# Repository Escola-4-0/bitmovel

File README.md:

# BitMóvel
Com esta placa você pode fazer um robô controlado pela micro:bit que é fácil de montar e programar com a extensão Escola 4.0 para o MakeCode. A própria placa serve como chassi do robô e dispensa o uso de conectores especiais para a micro:bit. A pasta [bitmovel](https://github.com/Escola-4-0/bitmovel/tree/main/bitmovel) contém o projeto da PCB para o KiCAD e arquivos gerber prontos para fabricação.

As peças `para-choque.stl` e `suporte-sensor.stl` podem ser impressas em 3D para caracterizar seu robô e fixar sensores para fazê-lo funcionar como um seguidor de linha. 

## Características da placa (v3)
- Placa em face simples;
- Componentes em PTH para facilicar a montagem manual;
- Fixação da micro:bit usando parafusos;
- Fornece alimentação regulada 3.3V para a micro:bit;
- CI ponte-h para dois motores DC;
- Permite a conexão de sensores para seguidor de linha.

## Lista de materiais

REF | componente
-- | --
C1 | Capacitor eletrolítico 10uF - 10V |
C2 | Capacitor eletrolítico 10uF - 10V |
C3 | Capacitor eletrolítico 10uF - 10V |
D1 | LED difuso 5mm
D2 | LED difuso 5mm
D3 | Diodo 1N5817 (1N5818 - 1N5822 compatíveis)
J1 | Módulo adaptador micro-USB fêmea para DIP (opcional)
R1 | Resistor 330Ω
R2 | Resistor 330Ω
SW1 | Chave HH SS12F46 - 3 terminais
U1 | LM1117-3.3 (regulador de tensão 3.3V)
U2 | L293D (driver para motor DC)

Para implementar a função de seguidor de linha, são necessários ainda **2 módulos de sensor infravermelho TCRT5000**.

## Descrição e funcionamento
Seis pinos da micro:bit fornecem os sinais de entrada do driver L293D que controla os motores, conforme a tabela: 

pino micro:bit | pino L293D
:--: | :--:
P0 | 2A
P1 | 1A
P2 | 4A
P8 | 1,2EN
P13 | 3A
P15 | 3,4EN

A micro:bit é alimentada pelo regulador LM1117 de 3.3V, o driver L293D e os LEDs são alimentados diretamente pela tensão de entrada, a fonte deve ser de 4.5 a 7V.

Os pinos P14 e P16 recebem os sinais digitais do sensor infravermelho direito e esquerdo, respectivamente.

## Programação
A tabela abaixo resume os comandos para acionamento dos motores:

P8 (P15) | P0 (P2) | P1 (P13) | motor D (motor E)
:--: | :--: | :--: | --
PWM | 1 | 0 | girar horário*
PWM | 0 | 1 | girar anti-horário*
1 | 1 | 1 | parada forçada
1 | 0 | 0 | parada forçada
0 | X | X | parada livre

*O sentido real depende da ligação do motor. X = não importa.

Os sinais dos sensores infravermelho seguem a lógica da tabela abaixo:

P14 (P16) | sensor D (sensor E)
:--: | :--:
0 | luz refletindo, superfície clara
1 | luz não refletindo, superfície escura

No MakeCode, o BitMóvel pode ser programado com os blocos `gravação digital pin` e `gravação analógica pin`, seguindo as combinações da tabela acima, ou com a [extensão Escola 4.0](https://github.com/Escola-4-0/pxt-Escola_4pontozero), usando os blocos da categoria "BitMóvel".

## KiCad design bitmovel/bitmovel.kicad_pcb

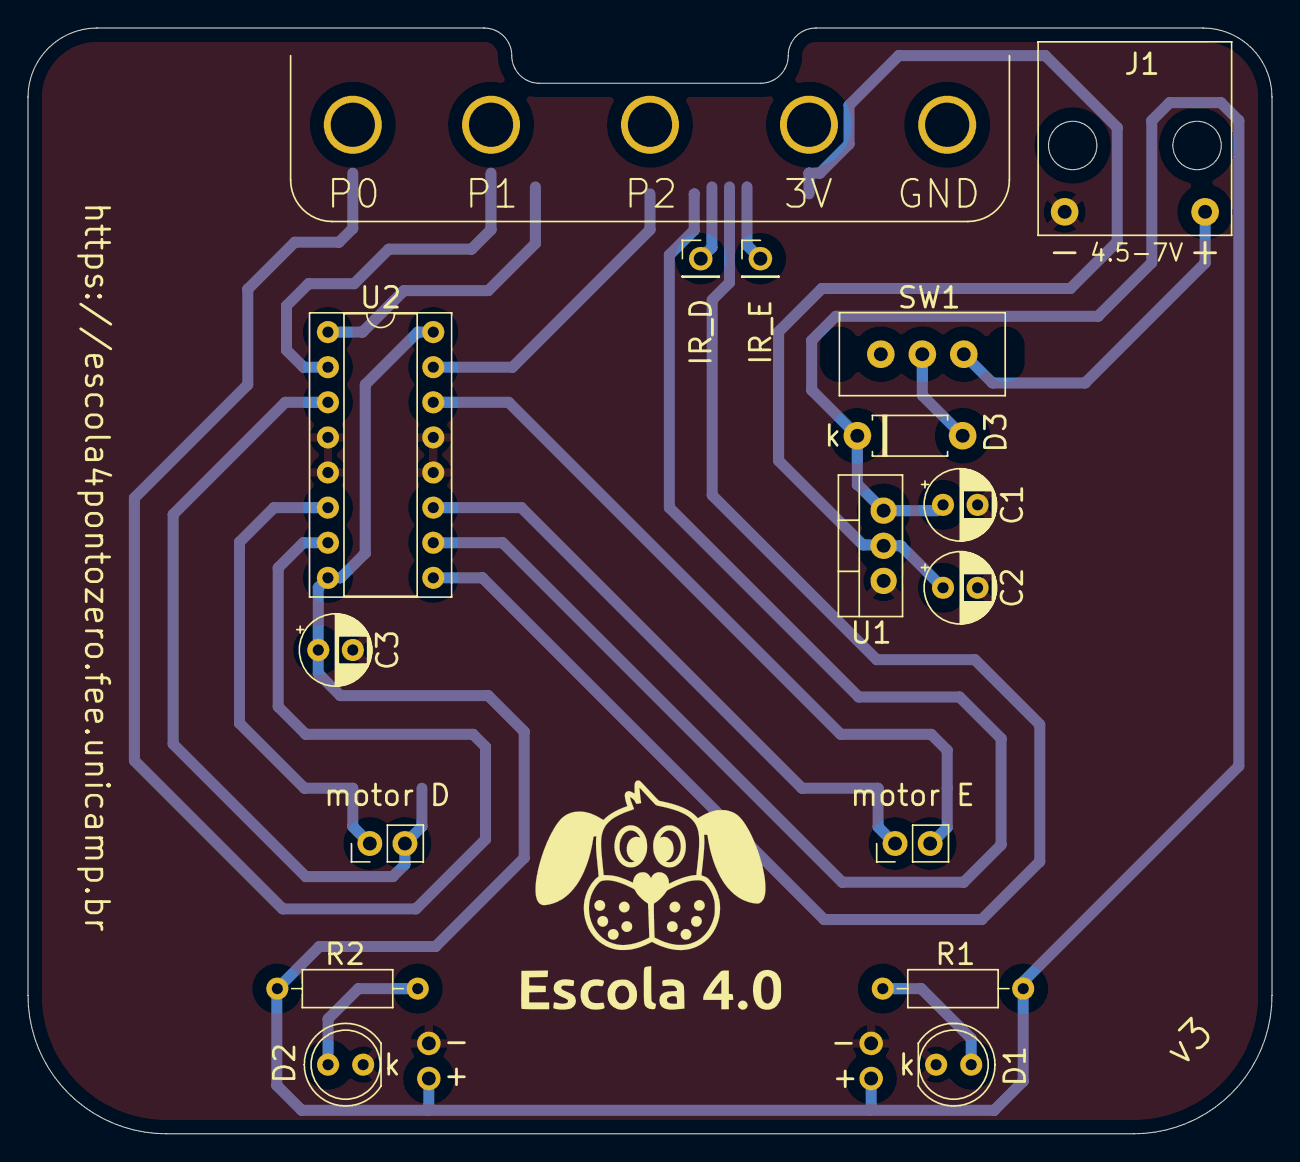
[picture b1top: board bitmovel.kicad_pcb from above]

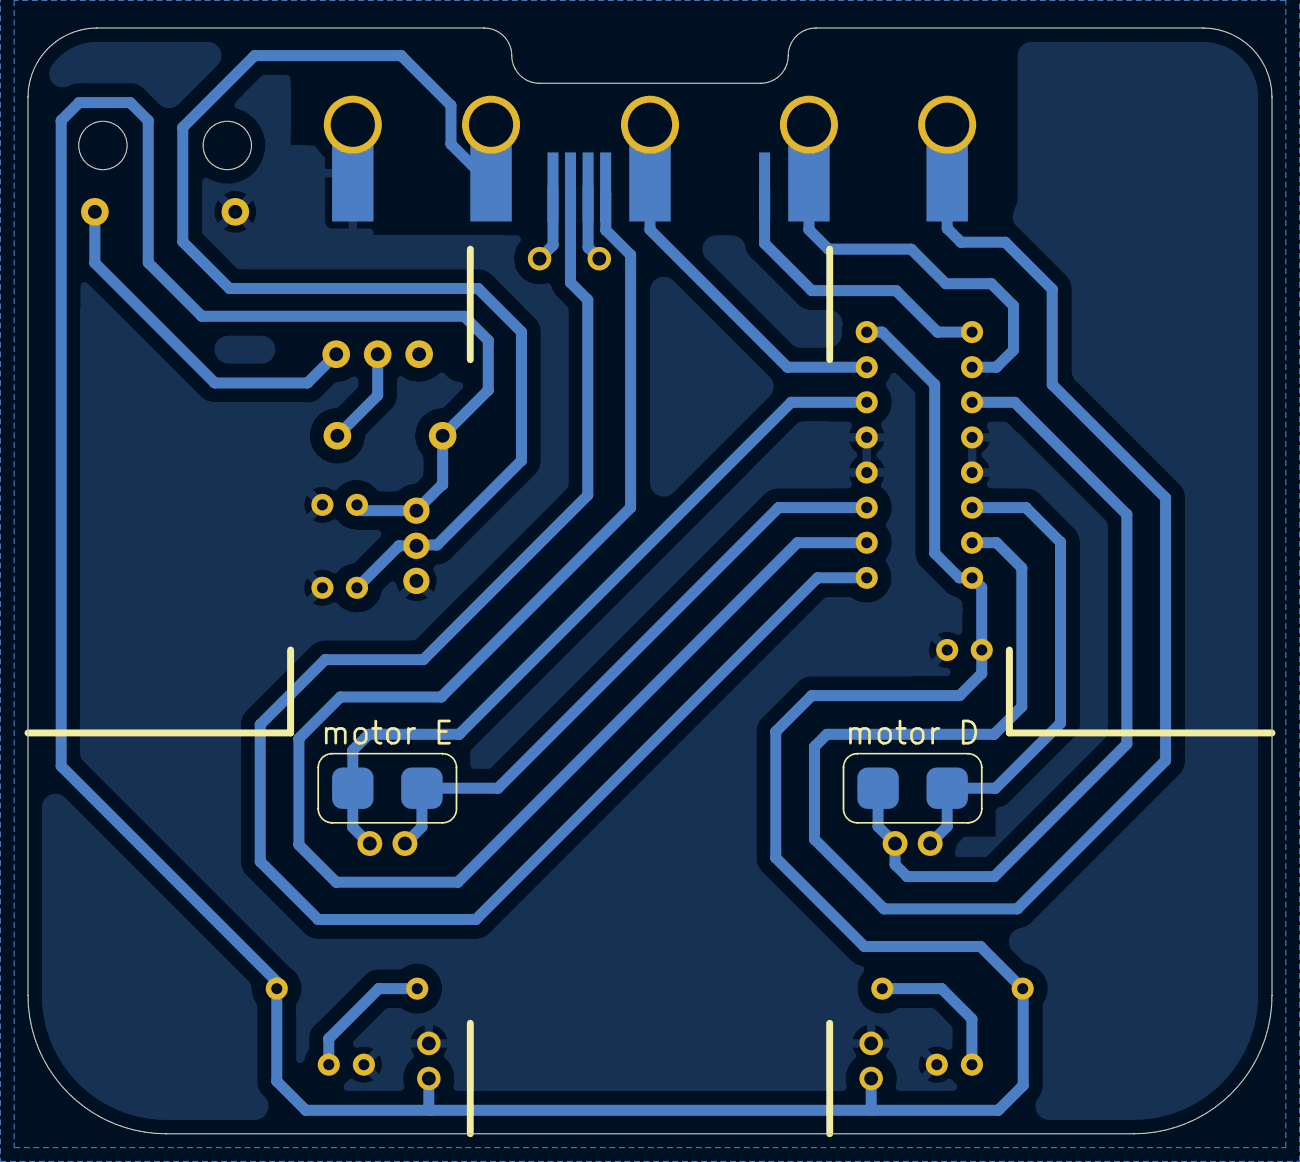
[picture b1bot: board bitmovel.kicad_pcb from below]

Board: 2 copper layers, 90.0 x 80.0 mm, 19 parts (2 on the bottom side), 19 nets.

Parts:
C1, C2, C3: 10uF; CP_Radial_D5.0mm_P2.50mm
D1, D2: LED; LED_D5.0mm
D3: D_Small; D_A-405_P7.62mm_Horizontal
J1: Conn_01x02_Male; microUSB-breakout-2pin
J2: micro:bit; microbit_edge_rings
J3: motor D; SolderJumper-2_P1.3mm_Open_RoundedPad1.0x1.5mm
J4: motor E; SolderJumper-2_P1.3mm_Open_RoundedPad1.0x1.5mm
J6, J9: Conn_01x02_Female; PinHeader_1x02_P2.54mm_Vertical
J7, J8: Conn_01x01_Female; PinHeader_1x01_P2.54mm_Vertical
R1, R2: R_US; R_Axial_DIN0207_L6.3mm_D2.5mm_P10.16mm_Horizontal
SW1: SW_SPST; Slide_Switch
U1: LM1117-3.3; TO-220-3_Vertical
U2: L293D; DIP-16_W7.62mm_Socket

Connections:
/3.3V: C2.1, J2.7, U1.2 (VO)
/Vin: C1.1, C3.1, D3.1 (K), J6.1, J9.1, R1.1, R2.1, U1.3 (VI), U2.8 (VCC2), U2.16 (VCC1)
GND: C1.2, C2.2, C3.2, D1.1 (K), D2.1 (K), J1.1, J2.8, J6.2, J9.2, U1.1 (GND), U2.4 (GND), U2.5 (GND), U2.12 (GND), U2.13 (GND)
unnamed: D1.2 (A), R1.2
unnamed: D2.2 (A), R2.2
unnamed: D3.2 (A), SW1.2 (B)
unnamed: J1.2, SW1.1 (A)
unnamed: J2.1, U2.7 (2A)
unnamed: J2.2, U2.2 (1A)
unnamed: J2.3, U2.1 (EN1,2)
unnamed: J2.4, U2.15 (4A)
unnamed: J2.5, U2.10 (3A)
unnamed: J2.6, U2.9 (EN3,4)
unnamed: J2.9, J8.1
unnamed: J2.10, J7.1
unnamed: J3.1, U2.3 (1Y)
unnamed: J3.2, U2.6 (2Y)
unnamed: J4.1, U2.11 (3Y)
unnamed: J4.2, U2.14 (4Y)

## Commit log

2021-04-08 Adicionando a licença Creative Commons Attribution Share Alike 4.0 International
2023-11-04 Atualizando URL e versão da placa impressas na silkscreen
2023-11-04 Remove arquivos inúteis
2023-11-05 atualizando arquivos gerber
2023-11-05 Atualizando README.md
2024-03-05 Adiciona pads P14 e P16 no footprint da microbit
2024-03-05 Inclui ilhas para conectar P14, P16, 3V3 e GND
2024-03-06 Inclui ilhas para conectar a Vin
2024-03-09 Remove arquivos legados
2024-03-09 Remove backups
2024-03-09 Corrige gitignore
2024-03-09 Corrige posição das ilhas 3v3 e GND
2024-03-11 Atualiza gerbers
2024-05-31 Atualiza versão para v3 e outros ajustes na silkscreen
2024-05-31 Atualiza gerbers com número de versão
2024-05-31 Inclui peças para impressão 3D
2024-05-31 Atualiza readme e pdfs
2024-05-31 Corrige arquivo 3D do suporte do sensor
